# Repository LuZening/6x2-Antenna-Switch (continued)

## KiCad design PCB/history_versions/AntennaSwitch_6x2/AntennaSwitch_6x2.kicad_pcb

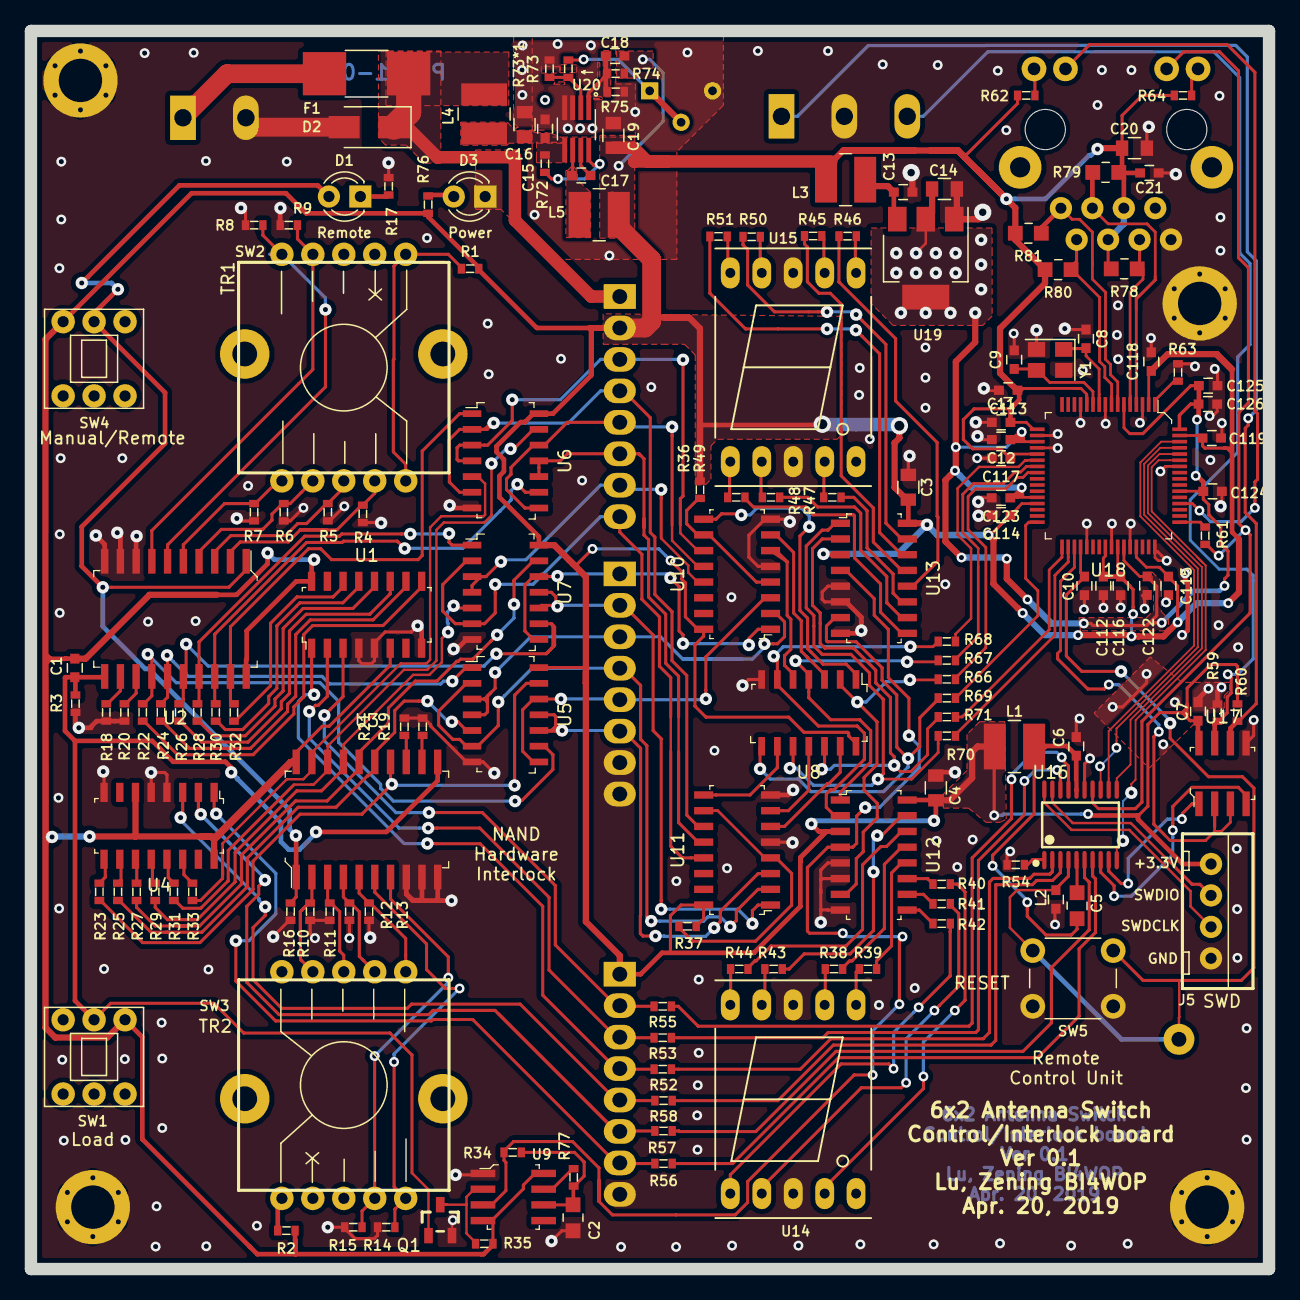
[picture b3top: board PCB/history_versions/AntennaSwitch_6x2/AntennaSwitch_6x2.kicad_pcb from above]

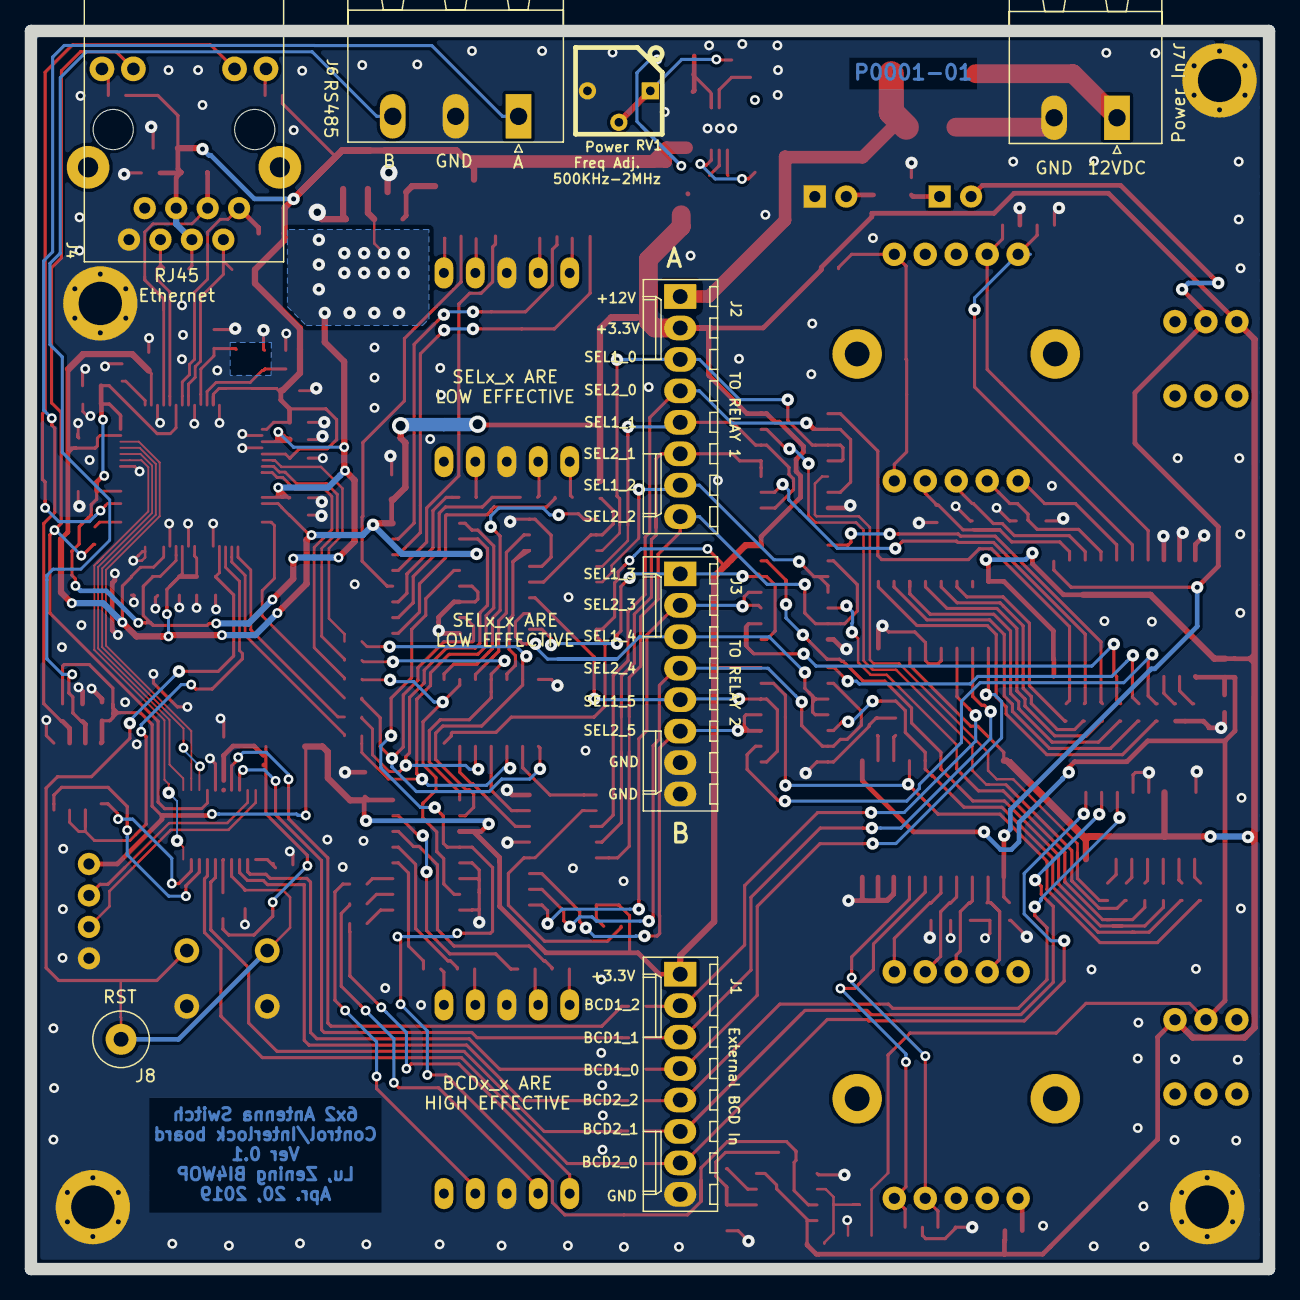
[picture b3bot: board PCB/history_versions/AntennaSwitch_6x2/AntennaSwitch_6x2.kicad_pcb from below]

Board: 2 copper layers, 100.0 x 100.0 mm, 161 parts (8 on the bottom side), 162 nets.

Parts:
C1, C5, C6, C7, C10, C11, C12, C13, C15, C21, C112, C113, C114, C115, C116, C117, C118, C119, C122, C123, C124, C125, C126: 104; C_0603
C2: 22uF; 0805
C3, C4: 4.7uF; C_0805
C8, C9: 20pF; C_0603
C14, C19: 22uF; C_0805
C16: 4.7uF 25V; C_0805
C17: 10nF; C_0603
C18: 47pF; C_0603
C20: 2.2uF; C_0805
D1: Green; LED_D3.0mm
D2: 16V; D_SMA
D3: Red; LED_D3.0mm
F1: 2A; R_1812_HandSoldering
J1, J2, J3: Conn_01x08; Molex_KK-6410-08_08x2.54mm_Straight
J4: HR913550A
J5: SWD; XH2.54-4
J6: 485; PhoenixContact_MSTBA-G_03x5.08mm_Angled
J7: 12VDC; PhoenixContact_MSTBA-G_02x5.08mm_Angled
J8: Conn_01x01; 1pin
L1, L3: 22uH; L_SMD4030_hand
L2: 47uH; 0805
L4, L5: 22uH 1A; L_SMD4030_hand
Q1: 2N7002; SOT-23(SOT-23-3)
R1, R2, R61, R77: 100; 0603
R3, R16: 47K; 0603
R4, R5, R6, R7, R8, R9, R10, R11, R12, R13, R14, R15, R18, R19, R20, R21, R22, R23, R24, R25, R26, R27, R28, R29, R30, R31, R32, R33, R36, R37, R52, R53, R54, R55, R56, R57, R58, R66, R67, R68, R69, R70, R71: 10K; 0603
R17: 220; 0603
R34: 470K; 0603
R35, R72, R73*1, R74: 100K; 0603
R38, R39, R40, R41, R42, R43, R44, R45, R46, R47, R48, R49, R50, R51: 33; 0603
R59, R60: 1K; 0603
R62, R64: 330; 0603
R63: 12K; 0603
R73: 51K; 0603
R75: 22K; 0603
R76: 300; 0603
R78, R79, R80, R81: 49.9; 0805
RV1: 100K; 3362P
SW1: LOAD; K8-7071
SW2, SW3: SRBV170501
SW4: M/R; K8-7071
SW5: RESET; SW_PUSH_6mm
U1, U4: 74HC238; SOIC-16_W3.90mm
U2, U3: 74HC573; SOIC-20_W7.5mm
U5, U6, U7: 74HC00; SOIC-14_W3.9mm
U8: 74HC04; SOIC-14_W3.9mm
U9: TLC555; SOIC-8_W3.9mm
U10, U11: 74HC148; SOIC-16_W3.90mm
U12, U13: 4511; SOIC-16_W3.90mm
U14, U15: Blue 0.56'' CC; 7SegmentLED_LTS6760_LTS6780
U16: STM32F030F4Px; TSSOP-20
U17: MAX485E; SOIC-8_W3.9mm
U18: CH395Q; LQFP-64_10x10mm
U19: AZ1117-1.8; SOT-223-3_TabPin2
U20: SY8303; TSOT-23-8_HandSoldering
Y1: 30MHz; Crystal_SMD_3225-4pin_3.2x2.5mm
e: M3_Screwhole

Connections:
+1V8: C12.1, C14.1, C122.1, C123.1, C124.1, C125.1, C126.1, U18.6, U18.19, U18.28, U18.43, U18.54, U18.64, U19.2
+3V3: C1.1, C3.2, C4.2, C7.2, C11.2, C18.1, C19.1, C20.1, C21.1, C112.1, C113.1, C114.1, C115.1, C116.1, C117.1, C118.1, C119.1, J1.1, J2.2, J4.4, J4.5, J5.1, L1.1, L3.1, L5.2, R1.1, R2.1, R35.1, R36.1, R37.1, R60.2, R62.2, R64.2, R74.1, R76.1, R78.2, R79.2, R80.2, R81.2, SW1.1, SW4.3, U1.6, U1.16, U2.20, U3.20, U4.6, U4.16, U5.14, U6.14, U7.14, U8.14, U9.4, U9.8, U10.16, U11.16, U12.3, U12.16, U13.3, U13.16, U17.8, U18.2, U18.12, U18.17, U18.21, U18.29, U18.40, U18.42, U18.45, U18.63
+12V: D2.1, F1.1, J2.1, L4.1
/Interlock/EnableRemote: D1.2, R16.1, SW4.2, U2.1, U3.1
/Interlock/Load: C1.2, Q1.1, R3.1, SW1.2, U2.11, U3.11
/Interlock/REMOTE1_0: R32.1, U1.14
/Interlock/REMOTE1_1: R30.1, U1.13
/Interlock/REMOTE1_2: R28.1, U1.12
/Interlock/REMOTE1_3: R26.1, U1.11
/Interlock/REMOTE1_4: R24.1, U1.10
/Interlock/REMOTE1_5: R22.1, U1.9
/Interlock/REMOTE2_0: R33.2, U4.14
/Interlock/REMOTE2_1: R31.2, U4.13
/Interlock/REMOTE2_2: R29.2, U4.12
/Interlock/REMOTE2_3: R27.2, U4.11
/Interlock/REMOTE2_4: R25.2, U4.10
/Interlock/REMOTE2_5: R23.2, U4.9
/Interlock/SELECT1_0: R32.2, U2.19, U6.1
/Interlock/SELECT1_1: R30.2, U2.18, U6.9
/Interlock/SELECT1_2: R28.2, U2.17, U7.1
/Interlock/SELECT1_3: R26.2, U2.16, U7.9
/Interlock/SELECT1_4: R24.2, U2.15, U5.1
/Interlock/SELECT1_5: R22.2, U2.14, U5.9
/Interlock/SELECT2_0: R33.1, U3.19, U6.5
/Interlock/SELECT2_1: R31.1, U3.18, U6.13
/Interlock/SELECT2_2: R29.1, U3.17, U7.5
/Interlock/SELECT2_3: R27.1, U3.16, U7.13
/Interlock/SELECT2_4: R25.1, U3.15, U5.5
/Interlock/SELECT2_5: R23.1, U3.14, U5.13
/Remote/485RW: U17.2, U17.3, U18.35
/Remote/A: J6.1, R60.1, U17.6
/Remote/B: J6.3, R59.2, U17.7
/Remote/INT: J4.11, R61.2, U16.14
/Remote/RST: C5.1, C10.1, J8.1, SW5.2, U16.4, U18.36
/Remote/RXD: U16.9, U17.1
/Remote/RXN: J4.6, R78.1, U18.5
/Remote/RXP: J4.3, R79.1, U18.4
/Remote/SPI_CS: U16.10, U18.59
/Remote/SPI_MISO: U16.12, U18.62
/Remote/SPI_MOSI: U16.13, U18.61
/Remote/SPI_SCK: U16.11, U18.60
/Remote/SWCLK: J5.3, U16.20
/Remote/SWDIO: J5.2, U16.19
/Remote/TXD: U16.8, U17.4
/Remote/TXN: J4.2, R80.1, U18.8
/Remote/TXP: J4.1, R81.1, U18.7
/Remote/X+: C8.1, U18.10, Y1.1
/Remote/X-: C9.1, U18.11, Y1.3
BCD1_0: J1.4, R52.2, U1.1
BCD1_1: J1.3, R53.2, U1.2
BCD1_2: J1.2, R55.1, U1.3
BCD2_0: J1.7, R56.1, U4.1
BCD2_1: J1.6, R57.1, U4.2
BCD2_2: J1.5, R58.1, U4.3
BCDM_1_0: R66.1, U8.2, U12.7
BCDM_1_1: R67.1, U8.4, U12.1
BCDM_1_2: R68.1, U8.6, U12.2
BCDM_2_0: R69.1, U8.8, U13.7
BCDM_2_1: R70.1, U8.10, U13.1
BCDM_2_2: R71.1, U8.12, U13.2
unnamed: C2.1, R34.2, R77.2, U9.6
unnamed: C6.1, L1.2, L2.1, U16.16
unnamed: C13.1, L3.2, U19.3
unnamed: C15.1, C16.1, L4.2, R72.1, U20.5
unnamed: C17.1, L5.1, U20.6
unnamed: C17.2, U20.7
unnamed: C18.2, R74.2, R75.1, U20.1
unnamed: D1.1, R17.1
unnamed: D3.2, R76.2
unnamed: F1.2, J7.1
unnamed: J2.3, U6.3, U6.4, U10.11
unnamed: J2.4, U6.2, U6.6, U11.11
unnamed: J2.5, U6.8, U6.12, U10.12
unnamed: J2.6, U6.10, U6.11, U11.12
unnamed: J2.7, U7.3, U7.4, U10.13
unnamed: J2.8, U7.2, U7.6, U11.13
unnamed: J3.1, U7.8, U7.12, U10.1
unnamed: J3.2, U7.10, U7.11, U11.1
unnamed: J3.3, U5.3, U5.4, U10.2
unnamed: J3.4, U5.2, U5.6, U11.2
unnamed: J3.5, U5.8, U5.12, U10.3
unnamed: J3.6, U5.10, U5.11, U11.3
unnamed: J4.9, R62.1
unnamed: J4.10, U18.52
unnamed: J4.12, R64.1
unnamed: L2.2, U16.5
unnamed: Q1.3, R35.2, U9.2
unnamed: R1.2, SW2.1, SW2.10
unnamed: R2.2, SW3.1, SW3.10
unnamed: R4.2, SW2.2, U2.2
unnamed: R5.2, SW2.3, U2.3
unnamed: R6.2, SW2.4, U2.4
unnamed: R7.2, SW2.5, U2.5
unnamed: R8.2, SW2.6, U2.6
unnamed: R9.2, SW2.7, U2.7
unnamed: R10.2, SW3.2, U3.2
unnamed: R11.2, SW3.3, U3.3
unnamed: R12.2, SW3.4, U3.4
unnamed: R13.2, SW3.5, U3.5
unnamed: R14.2, SW3.6, U3.6
unnamed: R15.2, SW3.7, U3.7
unnamed: R18.2, U2.12
unnamed: R19.1, U3.12
unnamed: R20.2, U2.13
unnamed: R21.1, U3.13
unnamed: R34.1, U9.3, U12.4, U13.4
unnamed: R36.2, U10.4, U10.10
unnamed: R37.2, U11.4, U11.10
unnamed: R38.1, U14.7
unnamed: R38.2, U12.13
unnamed: R39.1, U14.6
unnamed: R39.2, U12.12
unnamed: R40.1, U14.4
unnamed: R40.2, U12.11
unnamed: R41.1, U14.2
unnamed: R41.2, U12.10
unnamed: R42.1, U14.1
unnamed: R42.2, U12.9
unnamed: R43.1, U14.9
unnamed: R43.2, U12.15
unnamed: R44.1, U14.10
unnamed: R44.2, U12.14
unnamed: R45.1, U15.7
unnamed: R45.2, U13.13
unnamed: R46.1, U15.6
unnamed: R46.2, U13.12
unnamed: R47.1, U15.4
unnamed: R47.2, U13.11
unnamed: R48.1, U15.2
unnamed: R48.2, U13.10
unnamed: R49.1, U15.1
unnamed: R49.2, U13.9
unnamed: R50.1, U15.9
unnamed: R50.2, U13.15
unnamed: R51.1, U15.10
unnamed: R51.2, U13.14
unnamed: R52.1, U16.2
unnamed: R53.1, U16.18
unnamed: R54.2, U16.1
unnamed: R55.2, U16.17
unnamed: R56.2, U16.7
unnamed: R57.2, U16.6
unnamed: R58.2, U16.3
unnamed: R61.1, U18.49
unnamed: R63.2, U18.1
unnamed: R66.2, U18.24
unnamed: R67.2, U18.23
unnamed: R68.2, U18.22
unnamed: R69.2, U18.32
unnamed: R70.2, U18.34
unnamed: R71.2, U18.33
unnamed: R72.2, U20.8
unnamed: R73.1, R73*1.1, U20.2
unnamed: R73.2, RV1.1, RV1.2
unnamed: R77.1, U9.7
unnamed: U8.5, U10.6
unnamed: U8.3, U10.7
unnamed: U8.1, U10.9
unnamed: U8.13, U11.6
unnamed: U8.11, U11.7
unnamed: U8.9, U11.9
chasis: C2.2, C3.1, C4.1, C5.2, C6.2, C7.1, C8.2, C9.2, C10.2, C11.1, C12.2, C13.2, C14.2, C15.2, C16.2, C19.2, C20.2, C21.2, C112.2, C113.2, C114.2, C115.2, C116.2, C117.2, C118.2, C119.2, C122.2, C123.2, C124.2, C125.2, C126.2, D2.2, D3.1, J1.8, J3.7, J3.8, J4.8, J5.4, J6.2, J7.2, Q1.2, R3.2, R4.1, R5.1, R6.1, R7.1, R8.1, R9.1, R10.1, R11.1, R12.1, R13.1, R14.1, R15.1, R16.2, R17.2, R18.1, R19.2, R20.1, R21.2, R54.1, R59.1, R63.1, R73*1.2, R75.2, RV1.3, SW5.1, U1.4, U1.5, U1.8, U2.8, U2.9, U2.10, U3.8, U3.9, U3.10, U4.4, U4.5, U4.8, U5.7, U6.7, U7.7, U8.7, U9.1, U10.5, U10.8, U11.5, U11.8, U12.5, U12.6, U12.8, U13.5, U13.6, U13.8, U14.3, U14.8, U15.3, U15.8, U16.15, U17.5, U18.3, U18.9, U18.13, U18.18, U18.20, U18.37, U18.41, U18.44, U18.48, U18.58, U19.1, U20.3, U20.4, Y1.2, Y1.4, e.1

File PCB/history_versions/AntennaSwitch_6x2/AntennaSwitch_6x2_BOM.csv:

"Comment","Description","Designator","Footprint","LibRef","Pins","Quantity","PartNumber","url",
"104","desc","C126,C125,C124,C123,C122,C119,C118,C117,C116,C115,C114,C113,C112,C21,C15,C13,C12,C11,C10,C7,C6,C5,C1,","C_0603","libref","2","23","","",
"22uF","desc","C14,C19,","C_0805","libref","2","2","","",
"4.7uF 25V","desc","C16,","C_0805","libref","2","1","","",
"10nF","desc","C17,","C_0603","libref","2","1","","",
"47pF","desc","C18,","C_0603","libref","2","1","","",
"22uF","desc","C2,","0805","libref","2","1","","",
"2.2uF","desc","C20,","C_0805","libref","2","1","","",
"4.7uF","desc","C4,C3,","C_0805","libref","2","2","","",
"20pF","desc","C9,C8,","C_0603","libref","2","2","","",
"16V","desc","D2,","D_SMA","libref","2","1","","",
"2A","desc","F1,","R_1812_HandSoldering","libref","2","1","","",
"47uH","desc","L2,","0805","libref","2","1","","",
"22uH","desc","L3,L1,","L_SMD4030_hand","libref","2","2","","",
"22uH 1A","desc","L5,L4,","L_SMD4030_hand","libref","2","2","","",
"2N7002","desc","Q1,","SOT-23(SOT-23-3)","libref","3","1","","",
"47K","desc","R16,R3,","0603","libref","2","2","","",
"220","desc","R17,","0603","libref","2","1","","",
"470K","desc","R34,","0603","libref","2","1","","",
"33","desc","R51,R50,R49,R48,R47,R46,R45,R44,R43,R42,R41,R40,R39,R38,","0603","libref","2","14","","",
"10K","desc","R54,R66,R71,R70,R69,R68,R67,R58,R57,R56,R55,R53,R52,R37,R36,R33,R32,R31,R30,R29,R28,R27,R26,R25,R24,R23,R22,R21,R20,R19,R18,R15,R14,R13,R12,R11,R10,R9,R8,R7,R6,R5,R4,","0603","libref","2","43","","",
"1K","desc","R59,R60,","0603","libref","2","2","","",
"12K","desc","R63,","0603","libref","2","1","","",
"330","desc","R64,R62,","0603","libref","2","2","","",
"51K","desc","R73,","0603","libref","2","1","","",
"100K","desc","R73*1,R74,R72,R35,","0603","libref","2","4","","",
"22K","desc","R75,","0603","libref","2","1","","",
"300","desc","R76,","0603","libref","2","1","","",
"100","desc","R77,R61,R2,R1,","0603","libref","2","4","","",
"49.9","desc","R81,R80,R79,R78,","0805","libref","2","4","","",
"74HC148","desc","U11,U10,","SOIC-16_W3.90mm","libref","16","2","","",
"4511","desc","U13,U12,","SOIC-16_W3.90mm","libref","16","2","","",
"STM32F030F4Px","desc","U16,","TSSOP-20","libref","20","1","","",
"MAX485E","desc","U17,","SOIC-8_W3.9mm","libref","8","1","","",
"CH395Q","desc","U18,","LQFP-64_10x10mm","libref","64","1","","",
"AZ1117-1.8","desc","U19,","SOT-223-3_TabPin2","libref","4","1","","",
"SY8303","desc","U20,","TSOT-23-8_HandSoldering","libref","8","1","","",
"74HC573","desc","U3,U2,","SOIC-20_W7.5mm","libref","20","2","","",
"74HC238","desc","U4,U1,","SOIC-16_W3.90mm","libref","16","2","","",
"74HC00","desc","U7,U6,U5,","SOIC-14_W3.9mm","libref","14","3","","",
"74HC04","desc","U8,","SOIC-14_W3.9mm","libref","14","1","","",
"TLC555","desc","U9,","SOIC-8_W3.9mm","libref","8","1","","",
"30MHz","desc","Y1,","Crystal_SMD_3225-4pin_3.2x2.5mm","libref","4","1","","",
"Through Hole Items ",
"Green","desc","D1,","LED_D3.0mm","libref","2","1","","",
"Red","desc","D3,","LED_D3.0mm","libref","2","1","","",
"SWD","desc","J5,","XH2.54-4","libref","4","1","","",
"M3_Screwhole","desc","REF**,REF**,REF**,e,","M3_Screwhole","libref","7","4","","",
"LOAD","desc","SW1,","K8-7071","libref","6","1","","",
"SRBV170501","desc","SW2,SW3,","SRBV170501","libref","12","2","","",
"M/R","desc","SW4,","K8-7071","libref","6","1","","",
"RESET","desc","SW5,","SW_PUSH_6mm","libref","4","1","","",
"Blue 0.56'' CC","desc","U14,U15,","7SegmentLED_LTS6760_LTS6780","libref","10","2","","",
"Conn_01x08","desc","J3,J2,J1,","Molex_KK-6410-08_08x2.54mm_Straight","libref","8","3","","",
"HR913550A","desc","J4,","HR913550A","libref","16","1","","",
"485","desc","J6,","PhoenixContact_MSTBA-G_03x5.08mm_Angled","libref","3","1","","",
"12VDC","desc","J7,","PhoenixContact_MSTBA-G_02x5.08mm_Angled","libref","2","1","","",
"Conn_01x01","desc","J8,","1pin","libref","1","1","","",
"100K","desc","RV1,","3362P","libref","3","1","","",

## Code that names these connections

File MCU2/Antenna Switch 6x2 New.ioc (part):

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Mcu.Name=STM32F030C8Tx
Mcu.Package=LQFP48
Mcu.UserName=STM32F030C8Tx
PA1.GPIOParameters=GPIO_PuPd,GPIO_Label,GPIO_ModeDefaultEXTI
PA1.GPIO_Label=CH395_INT
PA1.GPIO_ModeDefaultEXTI=GPIO_MODE_IT_FALLING
PA1.GPIO_PuPd=GPIO_PULLUP
PA1.Signal=GPXTI1
PA10.GPIOParameters=PinState,GPIO_PuPd,GPIO_Label,GPIO_ModeDefaultOutputPP
PA10.GPIO_Label=BCD2_2
PA10.GPIO_ModeDefaultOutputPP=GPIO_MODE_OUTPUT_OD
PA10.GPIO_PuPd=GPIO_PULLUP
PA10.PinState=GPIO_PIN_SET
PA10.Signal=GPIO_Output
PA11.GPIOParameters=PinState,GPIO_PuPd,GPIO_Label,GPIO_ModeDefaultOutputPP
PA11.GPIO_Label=BCD2_1
PA11.GPIO_ModeDefaultOutputPP=GPIO_MODE_OUTPUT_OD
PA11.GPIO_PuPd=GPIO_PULLUP
PA11.PinState=GPIO_PIN_SET
PA11.Signal=GPIO_Output
PA12.GPIOParameters=PinState,GPIO_PuPd,GPIO_Label,GPIO_ModeDefaultOutputPP
PA12.GPIO_Label=BCD2_0
PA12.GPIO_ModeDefaultOutputPP=GPIO_MODE_OUTPUT_OD
PA12.GPIO_PuPd=GPIO_PULLUP
PA12.PinState=GPIO_PIN_SET
PA12.Signal=GPIO_Output
PA13.Mode=Serial_Wire
PA13.Signal=SYS_SWDIO
PA14.Mode=Serial_Wire
PA14.Signal=SYS_SWCLK
PA15.GPIOParameters=PinState,GPIO_PuPd,GPIO_Label,GPIO_ModeDefaultOutputPP
PA15.GPIO_Label=BCD1_2
PA15.GPIO_ModeDefaultOutputPP=GPIO_MODE_OUTPUT_OD
PA15.GPIO_PuPd=GPIO_PULLUP
PA15.PinState=GPIO_PIN_SET
PA15.Signal=GPIO_Output
PA2.GPIOParameters=GPIO_PuPd
PA2.GPIO_PuPd=GPIO_PULLUP
PA2.Mode=Asynchronous
PA2.Signal=USART2_TX
PA3.GPIOParameters=GPIO_PuPd
PA3.GPIO_PuPd=GPIO_PULLUP
PA3.Mode=Asynchronous
PA3.Signal=USART2_RX
PA4.GPIOParameters=PinState,GPIO_PuPd,GPIO_Label,GPIO_ModeDefaultOutputPP
PA4.GPIO_Label=SPI1_CS
PA4.GPIO_ModeDefaultOutputPP=GPIO_MODE_OUTPUT_OD
PA4.GPIO_PuPd=GPIO_PULLUP
PA4.PinState=GPIO_PIN_SET
PA4.Signal=GPIO_Output
PA5.GPIOParameters=GPIO_PuPd
PA5.GPIO_PuPd=GPIO_PULLUP
PA5.Mode=Full_Duplex_Master
PA5.Signal=SPI1_SCK
PA6.GPIOParameters=GPIO_PuPd
PA6.GPIO_PuPd=GPIO_PULLUP
PA6.Mode=Full_Duplex_Master
PA6.Signal=SPI1_MISO
PA7.GPIOParameters=GPIO_PuPd
PA7.GPIO_PuPd=GPIO_PULLUP
PA7.Mode=Full_Duplex_Master
PA7.Signal=SPI1_MOSI
PA8.GPIOParameters=GPIO_PuPd,GPIO_Label
PA8.GPIO_Label=BCDM1_1
PA8.GPIO_PuPd=GPIO_PULLUP
PA8.Signal=GPIO_Input
PA9.GPIOParameters=GPIO_PuPd,GPIO_Label
PA9.GPIO_Label=BCDM1_0
PA9.GPIO_PuPd=GPIO_PULLUP
PA9.Signal=GPIO_Input
PB10.GPIOParameters=PinState,GPIO_PuPd,GPIO_Label,GPIO_ModeDefaultOutputPP
PB10.GPIO_Label=XDISPLAY
PB10.GPIO_ModeDefaultOutputPP=GPIO_MODE_OUTPUT_OD
PB10.GPIO_PuPd=GPIO_PULLUP
PB10.PinState=GPIO_PIN_SET
PB10.Signal=GPIO_Output
PB11.GPIOParameters=PinState,GPIO_PuPd,GPIO_Label,GPIO_ModeDefaultOutputPP
PB11.GPIO_Label=RW485
PB11.GPIO_ModeDefaultOutputPP=GPIO_MODE_OUTPUT_PP
PB11.GPIO_PuPd=GPIO_NOPULL
PB11.PinState=GPIO_PIN_RESET
PB11.Signal=GPIO_Output
PB12.GPIOParameters=PinState,GPIO_PuPd,GPIO_Label,GPIO_ModeDefaultOutputPP
PB12.GPIO_Label=BCDM2_2
PB12.GPIO_ModeDefaultOutputPP=GPIO_MODE_OUTPUT_OD
PB12.GPIO_PuPd=GPIO_PULLUP
PB12.PinState=GPIO_PIN_SET
PB12.Signal=GPIO_Output
PB13.GPIOParameters=PinState,GPIO_PuPd,GPIO_Label,GPIO_ModeDefaultOutputPP
PB13.GPIO_Label=BCDM2_1
PB13.GPIO_ModeDefaultOutputPP=GPIO_MODE_OUTPUT_OD
PB13.GPIO_PuPd=GPIO_PULLUP
PB13.PinState=GPIO_PIN_SET
PB13.Signal=GPIO_Output
PB14.GPIOParameters=PinState,GPIO_PuPd,GPIO_Label,GPIO_ModeDefaultOutputPP
PB14.GPIO_Label=BCDM2_0
PB14.GPIO_ModeDefaultOutputPP=GPIO_MODE_OUTPUT_OD
PB14.GPIO_PuPd=GPIO_PULLUP
PB14.PinState=GPIO_PIN_SET
PB14.Signal=GPIO_Output
PB15.GPIOParameters=GPIO_PuPd,GPIO_Label
PB15.GPIO_Label=BCDM1_2
PB15.GPIO_PuPd=GPIO_PULLUP
PB15.Signal=GPIO_Input
PB3.GPIOParameters=PinState,GPIO_PuPd,GPIO_Label,GPIO_ModeDefaultOutputPP
PB3.GPIO_Label=BCD1_1
PB3.GPIO_ModeDefaultOutputPP=GPIO_MODE_OUTPUT_OD
PB3.GPIO_PuPd=GPIO_PULLUP
PB3.PinState=GPIO_PIN_SET
PB3.Signal=GPIO_Output
PB4.GPIOParameters=PinState,GPIO_PuPd,GPIO_Label,GPIO_ModeDefaultOutputPP
PB4.GPIO_Label=BCD1_0
PB4.GPIO_ModeDefaultOutputPP=GPIO_MODE_OUTPUT_OD
PB4.GPIO_PuPd=GPIO_PULLUP
PB4.PinState=GPIO_PIN_SET
PB4.Signal=GPIO_Output
PF0-OSC_IN.Signal=GPIO_Input
PF1-OSC_OUT.Signal=GPIO_Input
RCC.SYSCLKFreq_VALUE=48000000
RCC.SYSCLKSource=RCC_SYSCLKSOURCE_PLLCLK
board=custom

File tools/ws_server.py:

import asyncio
import websockets

HOST = '127.0.0.1'
PORT = 80
DISCONNECT_INTERVAL = 160  # 秒

async def disconnect_after(websocket):
    await asyncio.sleep(DISCONNECT_INTERVAL)
    print("为了测试，断开客户端连接。")
    await websocket.close()

async def handler(websocket):
    # 启动定时断开任务
    disconnect_task = asyncio.create_task(disconnect_after(websocket))
    try:
        while True:
            try:
                msg : str = await websocket.recv()
            except websockets.exceptions.ConnectionClosed:
                print("客户端已断开连接。")
                break

            print(f"收到客户端消息: {msg}")

            if msg.find("URI=/getalloc") >= 0:
                response = "URI=/getalloc&sel1=3&sel2=6"
            elif msg.find("URI=/switch") >= 0:
                response = "URI=/switch&response=OK"
            elif msg.find("URI=/getlabel") >= 0:
                response = "URI=/getlabel&ant1=ant1&ant2=ant2&ant3=ant3&ant4=ant4&ant5=ant5&ant6=ant6"
            elif msg.find("URI=/setlabel") >= 0:
                response = "URI=/setlabel&response=OK"
            elif msg.find("URI=/getport") >= 0:
                response = "URI=/getport&portHTTP=80&portTCP=23"
            elif msg.find("URI=/setport") >= 0:
                response = "URI=/setport&response=OK"
            elif msg.find("ping") >= 0:
                response = "pong"
            else:
                response = "Unknown command"

            await websocket.send(response)
    finally:
        disconnect_task.cancel()

async def main():
    async with websockets.serve(handler, HOST, PORT):
        print(f"WebSocket服务器已启动，地址为 ws://{HOST}:{PORT}")
        await asyncio.Future()  # 一直运行

if __name__ == "__main__":
    asyncio.run(main())

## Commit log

2019-04-14 SCH and PCB
2019-05-01 Relay Board SCH
2019-05-01 Relay Board PCB first draft
2019-06-08 manufacturing files
2019-09-17 FS Tools
2019-09-23 First attemp
2019-09-27 HTTP server finished
2019-09-28 EEPROM
2019-10-17 review on 19.10.18
2019-11-01 New control board design
2019-11-01 Control Board 2 routed
2019-12-11 final
2024-03-04 2024 ver
2025-07-21 Start to add support for WebSocket
2025-10-19 Add support for RS485
2026-03-30 Add support to socket status display
